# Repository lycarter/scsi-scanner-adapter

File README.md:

# scsi-scanner-adapter

Bringing a Howtek Scanmaster D4000 drum scanner (1990s, SCSI-2) to modern computers
with custom hardware (USB-C ↔ SCSI) and open scanning software.

## Status

Phase 0: requirements and architecture decisions.

## Phases

| # | Folder | What |
|---|--------|------|
| 1 | [`design_docs/1-bus-capture/`](design_docs/1-bus-capture/NOTES.md) | Logic analyzer, passive tap and capture tooling for watching the G4 ↔ scanner bus |
| 2 | [`design_docs/2-reverse-engineering/`](design_docs/2-reverse-engineering/NOTES.md) | Decode the command set and data flow (bus captures + firmware/software analysis) |
| 3 | [`design_docs/3-driver/`](design_docs/3-driver/NOTES.md) | USB-C ↔ SCSI initiator PCB that also works as a listen-only bus sniffer |
| 4 | [`design_docs/4-software/`](design_docs/4-software/NOTES.md) | Driver firmware and host scanning software |

Shared background: [`docs/scanner-facts.md`](docs/scanner-facts.md), [`docs/reference-inventory.md`](docs/reference-inventory.md), [`docs/decisions.md`](docs/decisions.md).

## Known-good baseline

A Power Mac G4 on Mac OS 9, running SilverFast, scans successfully with this scanner.

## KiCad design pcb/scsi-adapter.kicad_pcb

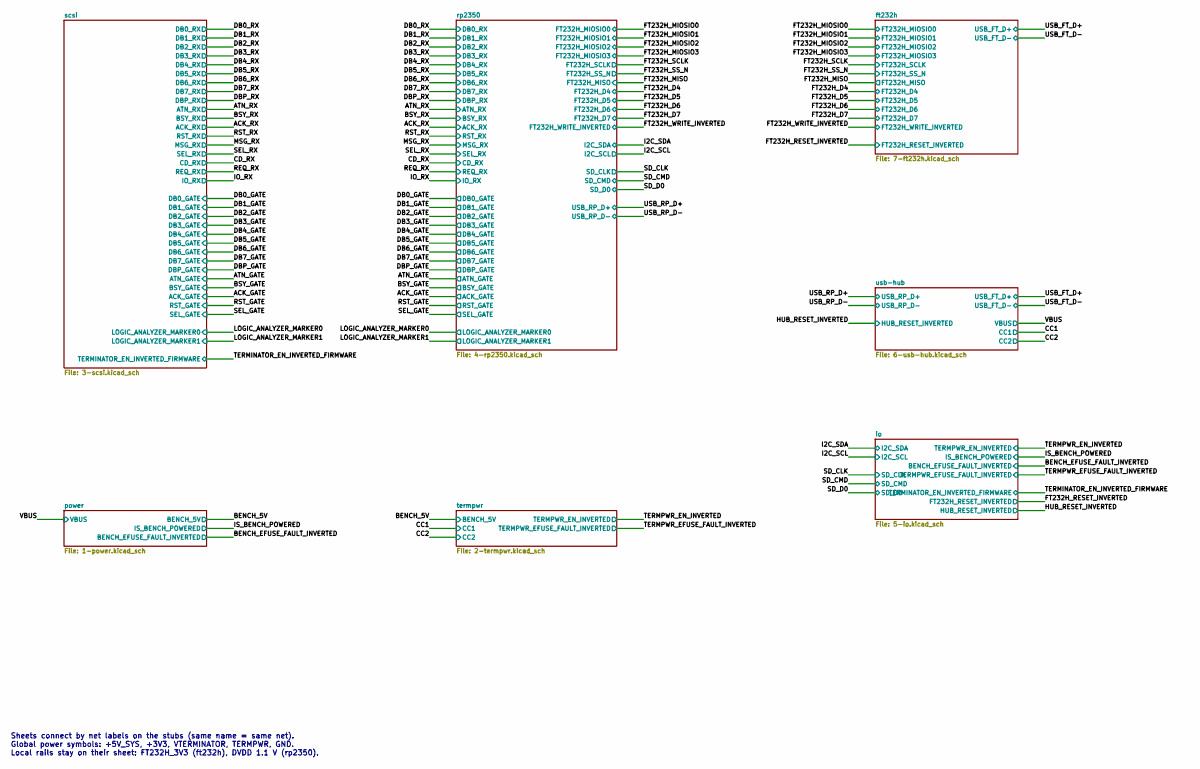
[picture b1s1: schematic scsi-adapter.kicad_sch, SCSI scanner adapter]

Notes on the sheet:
Sheets connect by net labels on the stubs (same name = same net). Global power symbols: +5V_SYS, +3V3, VTERMINATOR, TERMPWR, GND. Local rails stay on their sheet: FT232H_3V3 (ft232h), DVDD 1.1 V (rp2350).

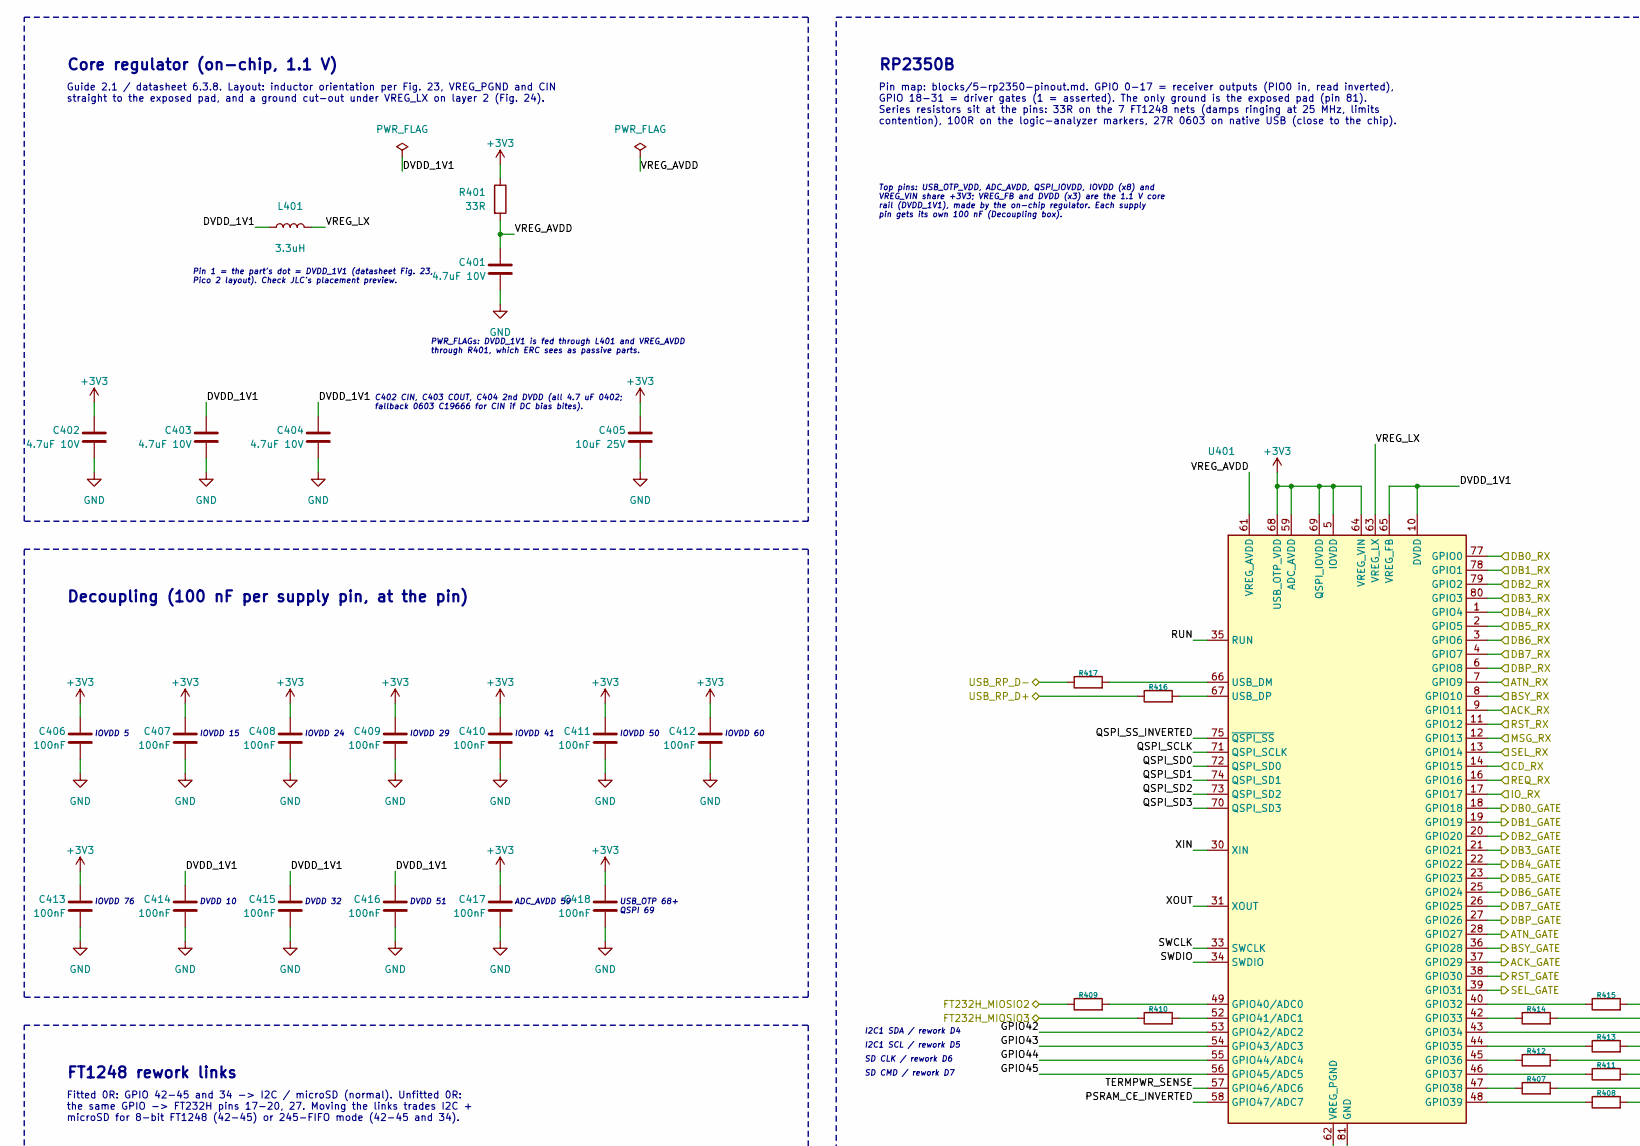
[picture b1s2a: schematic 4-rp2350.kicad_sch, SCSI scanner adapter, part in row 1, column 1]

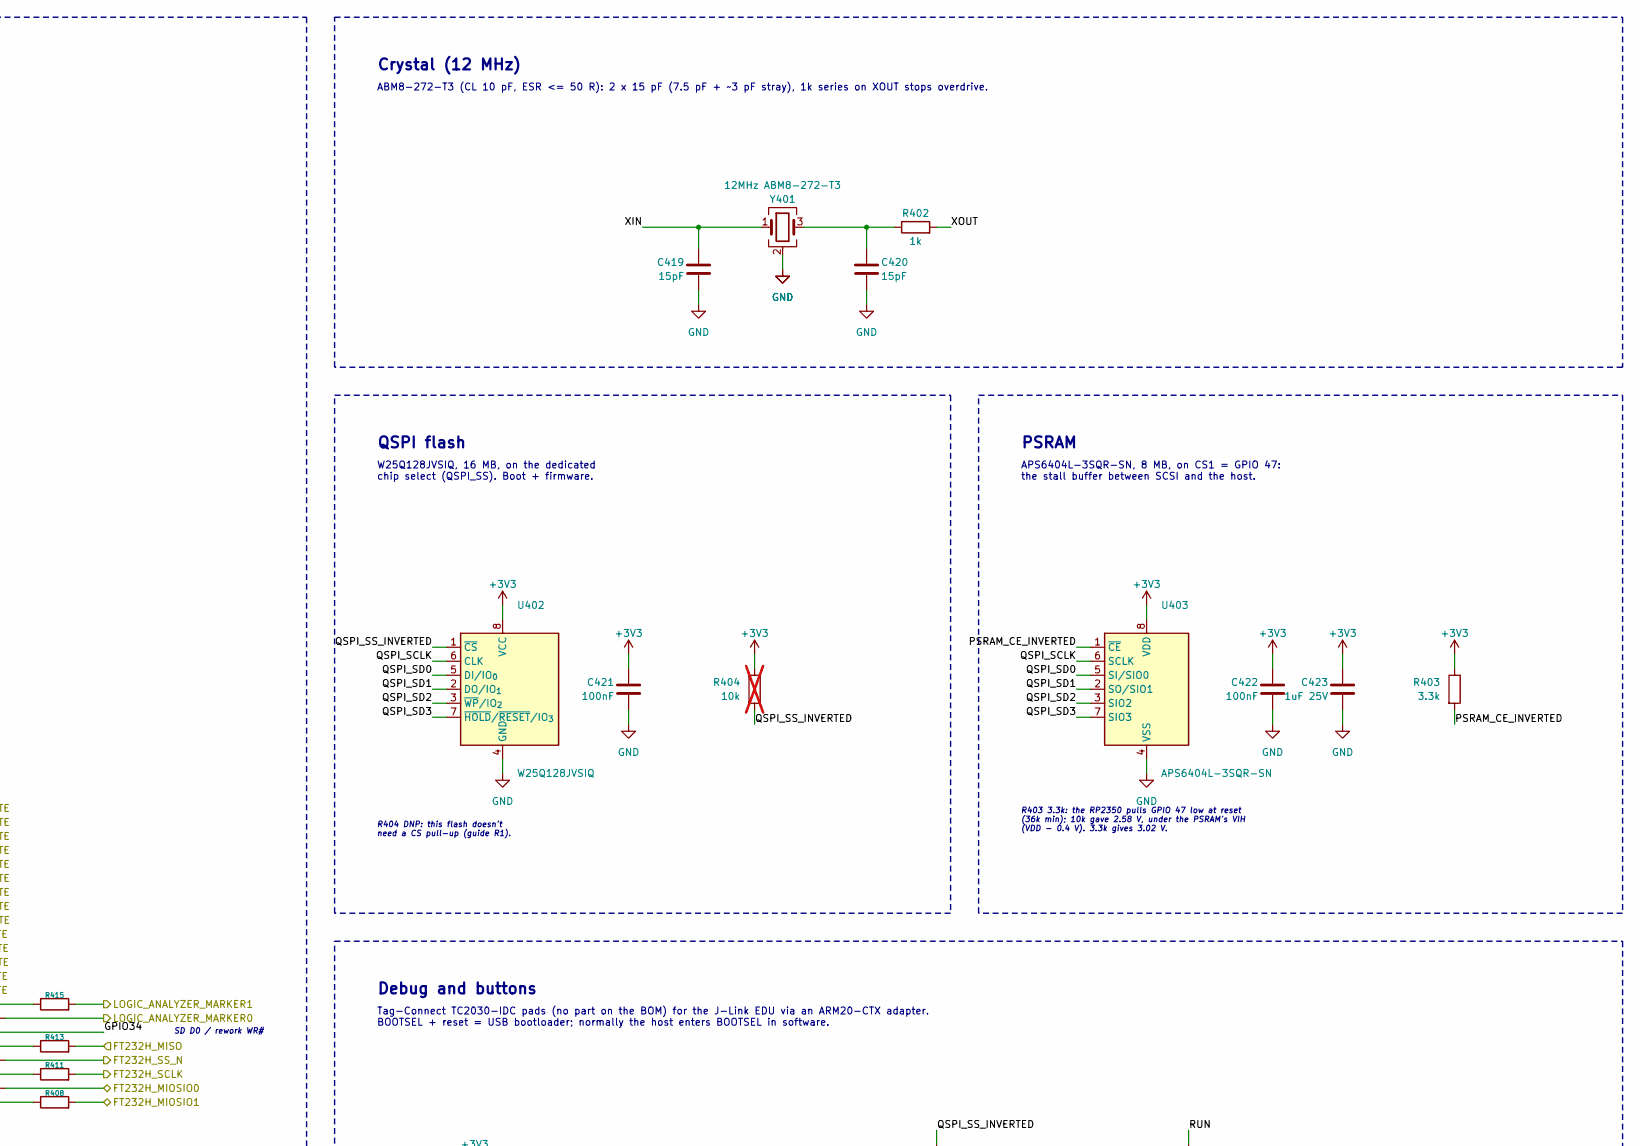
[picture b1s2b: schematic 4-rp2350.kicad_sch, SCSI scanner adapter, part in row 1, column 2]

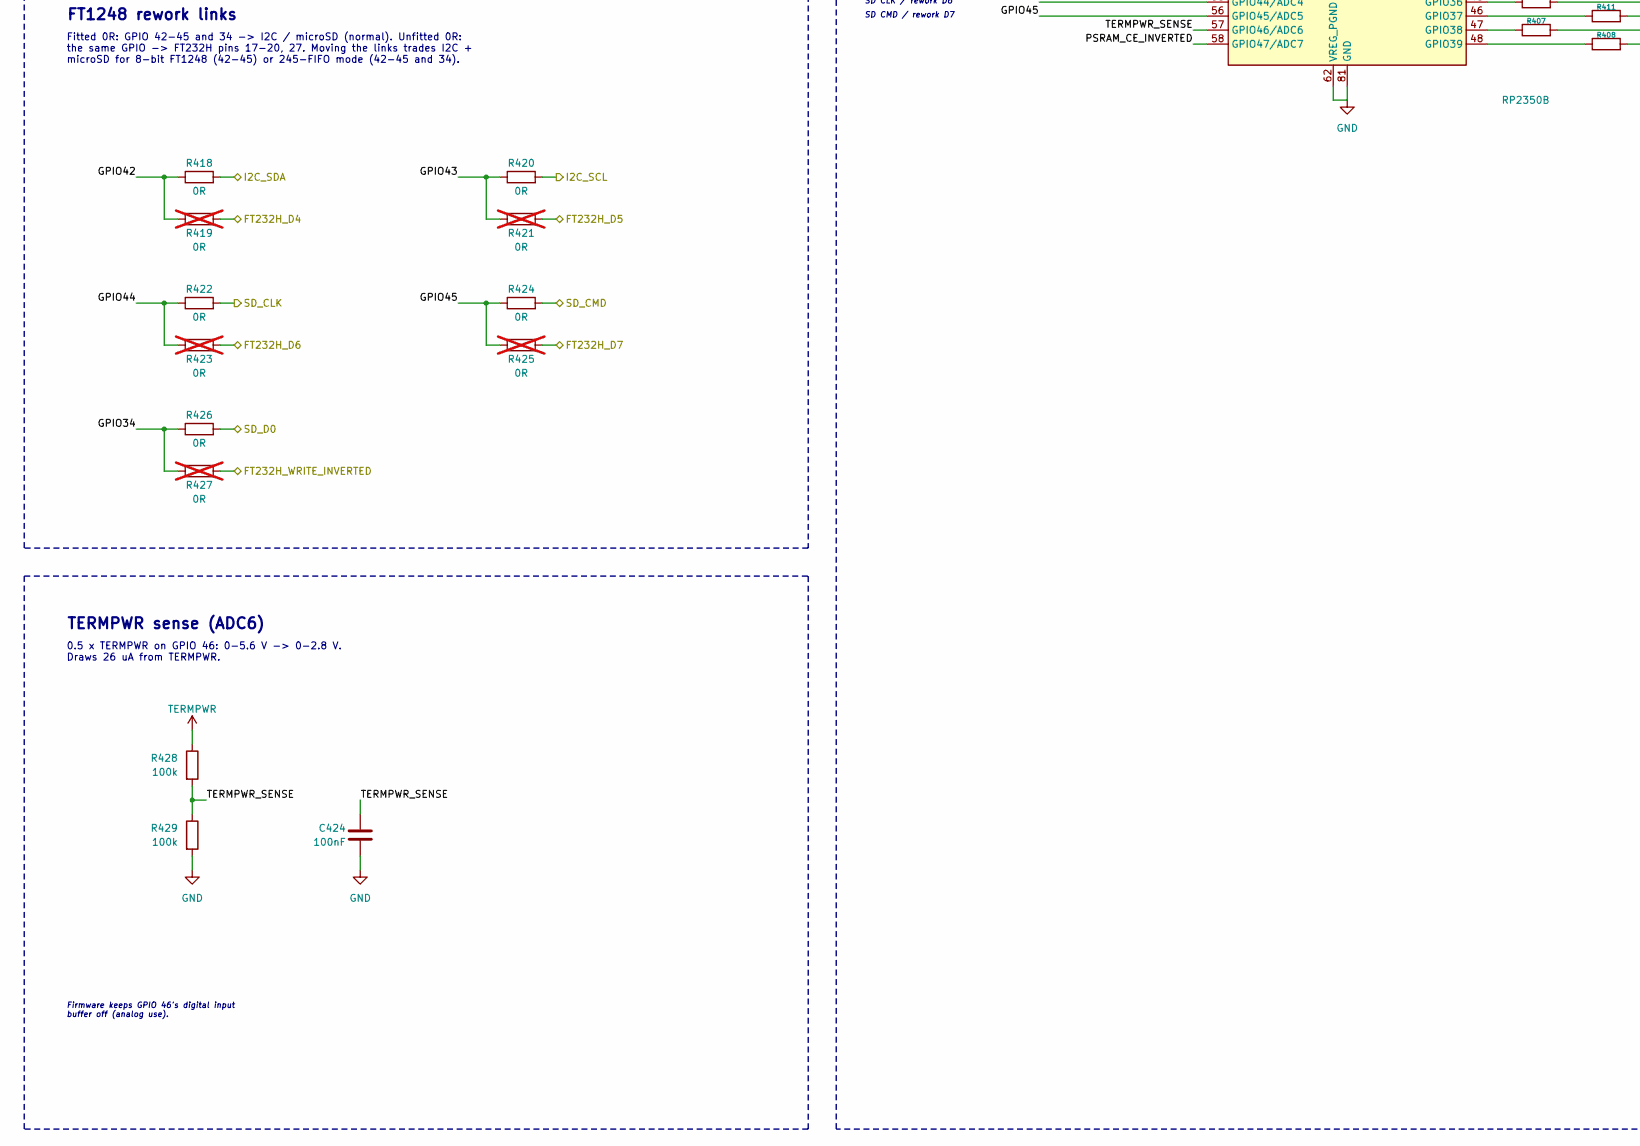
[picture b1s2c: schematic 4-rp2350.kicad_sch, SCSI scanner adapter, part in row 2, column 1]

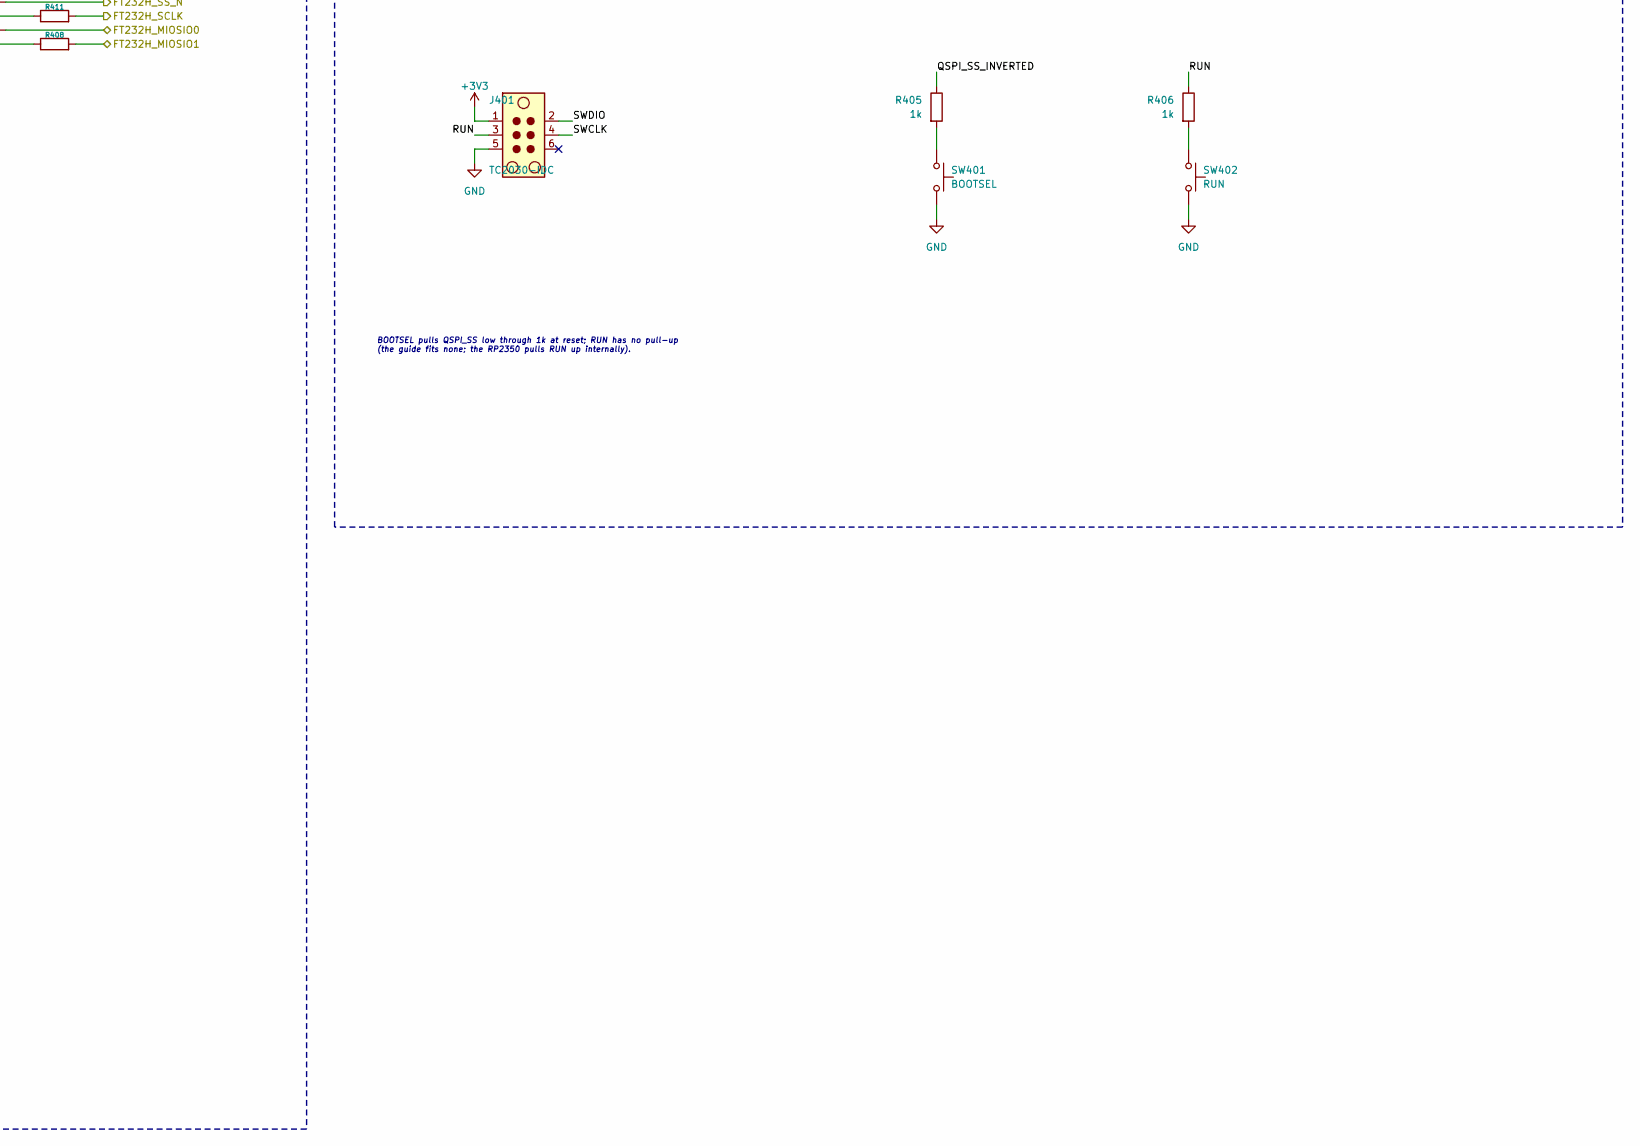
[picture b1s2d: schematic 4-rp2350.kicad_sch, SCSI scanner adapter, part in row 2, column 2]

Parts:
C401, C404: 4.7uF 10V; C_0402_1005Metric; LCSC C23733
C402, C403: 4.7uF 10V; C_0402_1005Metric_Wide; LCSC C23733
C405: 10uF 25V; C_0805_2012Metric; LCSC C15850
C406, C407, C408, C409, C410, C411, C412, C413, C414, C415, C416, C417, C418, C421, C422, C424: 100nF; C_0402_1005Metric; LCSC C307331
C419, C420: 15pF; C_0402_1005Metric; LCSC C1548
C423: 1uF 25V; C_0402_1005Metric; LCSC C52923
J401: TC2030-IDC; Tag-Connect_TC2030-IDC-FP_2x03_P1.27mm_Vertical
L401: 3.3uH; L_Abracon_AOTA-B201610_2.0x1.6mm_Polarized; LCSC C42411119
R401, R407, R408, R409, R410, R411, R412, R413: 33R; R_0402_1005Metric; LCSC C25105
R402, R405, R406: 1k; R_0402_1005Metric; LCSC C11702
R403: 3.3k; R_0402_1005Metric; LCSC C25890
R404: 10k; R_0402_1005Metric; LCSC C25744; not fitted
R414, R415: 100R; R_0402_1005Metric; LCSC C25076
R416, R417: 27R; R_0603_1608Metric; LCSC C25190
R418, R420, R422, R424, R426: 0R; R_0402_1005Metric; LCSC C17168
R419, R421, R423, R425, R427: 0R; R_0805_2012Metric; LCSC C17477; not fitted
R428, R429: 100k; R_0402_1005Metric; LCSC C25741
SW401: BOOTSEL; SW_PUSH_6mm; LCSC C110153
SW402: RUN; SW_PUSH_6mm; LCSC C110153
U401: RP2350B; QFN-80-1EP_10x10mm_P0.4mm_EP3.4x3.4mm; LCSC C42415655
U402: W25Q128JVSIQ; SOIC-8_5.3x5.3mm_P1.27mm; LCSC C97521
U403: APS6404L-3SQR-SN; SOIC-8_3.9x4.9mm_P1.27mm; LCSC C5333729
Y401: 12MHz ABM8-272-T3; Crystal_SMD_3225-4Pin_3.2x2.5mm; LCSC C20625731

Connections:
+3V3: C402.1, C405.1, C406.1, C407.1, C408.1, C409.1, C410.1, C411.1, C412.1, C413.1, C417.1, C418.1, C421.1, C422.1, C423.1, J401.1, R401.1, R403.1, R404.1, U401.5 (IOVDD), U401.15 (IOVDD), U401.24 (IOVDD), U401.29 (IOVDD), U401.41 (IOVDD), U401.50 (IOVDD), U401.59 (ADC_AVDD), U401.60 (IOVDD), U401.64 (VREG_VIN), U401.68 (USB_OTP_VDD), U401.69 (QSPI_IOVDD), U401.76 (IOVDD), U402.8 (VCC), U403.8 (VDD); also elsewhere on the board
/ACK_GATE: U401.37 (GPIO29); also elsewhere on the board
/ACK_RX: U401.9 (GPIO11); also elsewhere on the board
/ATN_GATE: U401.28 (GPIO27); also elsewhere on the board
/ATN_RX: U401.7 (GPIO9); also elsewhere on the board
/BSY_GATE: U401.36 (GPIO28); also elsewhere on the board
/BSY_RX: U401.8 (GPIO10); also elsewhere on the board
/CD_RX: U401.14 (GPIO15); also elsewhere on the board
/DB0_GATE: U401.18 (GPIO18); also elsewhere on the board
/DB0_RX: U401.77 (GPIO0); also elsewhere on the board
/DB1_GATE: U401.19 (GPIO19); also elsewhere on the board
/DB1_RX: U401.78 (GPIO1); also elsewhere on the board
/DB2_GATE: U401.20 (GPIO20); also elsewhere on the board
/DB2_RX: U401.79 (GPIO2); also elsewhere on the board
/DB3_GATE: U401.21 (GPIO21); also elsewhere on the board
/DB3_RX: U401.80 (GPIO3); also elsewhere on the board
/DB4_GATE: U401.22 (GPIO22); also elsewhere on the board
/DB4_RX: U401.1 (GPIO4); also elsewhere on the board
/DB5_GATE: U401.23 (GPIO23); also elsewhere on the board
/DB5_RX: U401.2 (GPIO5); also elsewhere on the board
/DB6_GATE: U401.25 (GPIO24); also elsewhere on the board
/DB6_RX: U401.3 (GPIO6); also elsewhere on the board
/DB7_GATE: U401.26 (GPIO25); also elsewhere on the board
/DB7_RX: U401.4 (GPIO7); also elsewhere on the board
/DBP_GATE: U401.27 (GPIO26); also elsewhere on the board
/DBP_RX: U401.6 (GPIO8); also elsewhere on the board
/FT232H_D4: R419.2; also elsewhere on the board
/FT232H_D5: R421.2; also elsewhere on the board
/FT232H_D6: R423.2; also elsewhere on the board
/FT232H_D7: R425.2; also elsewhere on the board
/FT232H_MIOSIO0: R407.2; also elsewhere on the board
/FT232H_MIOSIO1: R408.2; also elsewhere on the board
/FT232H_MIOSIO2: R409.1; also elsewhere on the board
/FT232H_MIOSIO3: R410.1; also elsewhere on the board
/FT232H_MISO: R413.2; also elsewhere on the board
/FT232H_SCLK: R411.2; also elsewhere on the board
/FT232H_SS_N: R412.2; also elsewhere on the board
/FT232H_WRITE_INVERTED: R427.2; also elsewhere on the board
/I2C_SCL: R420.2; also elsewhere on the board
/I2C_SDA: R418.2; also elsewhere on the board
/IO_RX: U401.17 (GPIO17); also elsewhere on the board
/LOGIC_ANALYZER_MARKER0: R414.2; also elsewhere on the board
/LOGIC_ANALYZER_MARKER1: R415.2; also elsewhere on the board
/MSG_RX: U401.12 (GPIO13); also elsewhere on the board
/REQ_RX: U401.16 (GPIO16); also elsewhere on the board
/RST_GATE: U401.38 (GPIO30); also elsewhere on the board
/RST_RX: U401.11 (GPIO12); also elsewhere on the board
/SD_CLK: R422.2; also elsewhere on the board
/SD_CMD: R424.2; also elsewhere on the board
/SD_D0: R426.2; also elsewhere on the board
/SEL_GATE: U401.39 (GPIO31); also elsewhere on the board
/SEL_RX: U401.13 (GPIO14); also elsewhere on the board
/USB_RP_D+: R416.1; also elsewhere on the board
/USB_RP_D-: R417.1; also elsewhere on the board
/rp2350/DVDD_1V1: C403.1, C404.1, C414.1, C415.1, C416.1, L401.1, U401.10 (DVDD), U401.32 (DVDD), U401.51 (DVDD), U401.65 (VREG_FB)
/rp2350/GPIO34: R426.1, R427.1, U401.43 (GPIO34)
/rp2350/GPIO42: R418.1, R419.1, U401.53 (GPIO42/ADC2)
/rp2350/GPIO43: R420.1, R421.1, U401.54 (GPIO43/ADC3)
/rp2350/GPIO44: R422.1, R423.1, U401.55 (GPIO44/ADC4)
/rp2350/GPIO45: R424.1, R425.1, U401.56 (GPIO45/ADC5)
/rp2350/PSRAM_CE_INVERTED: R403.2, U401.58 (GPIO47/ADC7), U403.1 (~CE)
/rp2350/QSPI_SCLK: U401.71 (QSPI_SCLK), U402.6 (CLK), U403.6 (SCLK)
/rp2350/QSPI_SD0: U401.72 (QSPI_SD0), U402.5 (DI/IO_{0}), U403.5 (SI/SIO0)
/rp2350/QSPI_SD1: U401.74 (QSPI_SD1), U402.2 (DO/IO_{1}), U403.2 (SO/SIO1)
/rp2350/QSPI_SD2: U401.73 (QSPI_SD2), U402.3 (~WP/IO_{2}), U403.3 (SIO2)
/rp2350/QSPI_SD3: U401.70 (QSPI_SD3), U402.7 (~HOLD/~RESET/IO_{3}), U403.7 (SIO3)
/rp2350/QSPI_SS_INVERTED: R404.2, R405.1, U401.75 (~QSPI_SS), U402.1 (~CS)
/rp2350/RUN: J401.3, R406.1, U401.35 (RUN)
/rp2350/SWCLK: J401.4, U401.33 (SWCLK)
/rp2350/SWDIO: J401.2, U401.34 (SWDIO)
/rp2350/TERMPWR_SENSE: C424.1, R428.2, R429.1, U401.57 (GPIO46/ADC6)
/rp2350/VREG_AVDD: C401.1, R401.2, U401.61 (VREG_AVDD)
/rp2350/VREG_LX: L401.2, U401.63 (VREG_LX)
/rp2350/XIN: C419.1, U401.30 (XIN), Y401.1
/rp2350/XOUT: R402.2, U401.31 (XOUT)
GND: C401.2, C402.2, C403.2, C404.2, C405.2, C406.2, C407.2, C408.2, C409.2, C410.2, C411.2, C412.2, C413.2, C414.2, C415.2, C416.2, C417.2, C418.2, C419.2, C420.2, C421.2, C422.2, C423.2, C424.2, J401.5, R429.2, SW401.2, SW402.2, U401.62 (VREG_PGND), U401.81 (GND), U402.4 (GND), U403.4 (VSS), Y401.2 (G), Y401.4 (G); also elsewhere on the board
unnamed: C420.1, R402.1, Y401.3
unnamed: R405.2, SW401.1
unnamed: R406.2, SW402.1
unnamed: R415.1, U401.40 (GPIO32)
unnamed: R414.1, U401.42 (GPIO33)
unnamed: R413.1, U401.44 (GPIO35)
unnamed: R412.1, U401.45 (GPIO36)
unnamed: R411.1, U401.46 (GPIO37)
unnamed: R407.1, U401.47 (GPIO38)
unnamed: R408.1, U401.48 (GPIO39)
unnamed: R409.2, U401.49 (GPIO40/ADC0)
unnamed: R410.2, U401.52 (GPIO41/ADC1)
unnamed: R417.2, U401.66 (USB_DM)
unnamed: R416.2, U401.67 (USB_DP)
TERMPWR: R428.1; also elsewhere on the board

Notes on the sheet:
BOOTSEL pulls QSPI_SS low through 1k at reset; RUN has no pull-up (the guide fits none; the RP2350 pulls RUN up internally).
USB_OTP 68+ QSPI 69
R404 DNP: this flash doesn't need a CS pull-up (guide R1).
PWR_FLAGs: DVDD_1V1 is fed through L401 and VREG_AVDD through R401, which ERC sees as passive parts.
ADC_AVDD 59
SD CLK / rework D6
I2C1 SDA / rework D4
Tag-Connect TC2030-IDC pads (no part on the BOM) for the J-Link EDU via an ARM20-CTX adapter. BOOTSEL + reset = USB bootloader; normally the host enters BOOTSEL in software.
Pin map: blocks/5-rp2350-pinout.md. GPIO 0-17 = receiver outputs (PIO0 in, read inverted), GPIO 18-31 = driver gates (1 = asserted). The only ground is the exposed pad (pin 81). Series resistors sit at the pins: 33R on the 7 FT1248 nets (damps ringing at 25 MHz, limits contention), 100R on the logi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
IOVDD 41
IOVDD 24
Firmware keeps GPIO 46's digital input buffer off (analog use).
IOVDD 50
W25Q128JVSIQ, 16 MB, on the dedicated chip select (QSPI_SS). Boot + firmware.
IOVDD 29
DVDD 10
Fitted 0R: GPIO 42-45 and 34 -> I2C / microSD (normal). Unfitted 0R: the same GPIO -> FT232H pins 17-20, 27. Moving the links trades I2C + microSD for 8-bit FT1248 (42-45) or 245-FIFO mode (42-45 and 34).
DVDD 51
ABM8-272-T3 (CL 10 pF, ESR <= 50 R): 2 x 15 pF (7.5 pF + ~3 pF stray), 1k series on XOUT stops overdrive.
Pin 1 = the part's dot = DVDD_1V1 (datasheet Fig. 23, Pico 2 layout). Check JLC's placement preview.
IOVDD 15
Guide 2.1 / datasheet 6.3.8. Layout: inductor orientation per Fig. 23, VREG_PGND and CIN straight to the exposed pad, and a ground cut-out under VREG_LX on layer 2 (Fig. 24).
PSRAM
APS6404L-3SQR-SN, 8 MB, on CS1 = GPIO 47: the stall buffer between SCSI and the host.
QSPI flash
IOVDD 76
SD CMD / rework D7
Core regulator (on-chip, 1.1 V)
FT1248 rework links
R403 3.3k: the RP2350 pulls GPIO 47 low at reset (36k min); 10k gave 2.58 V, under the PSRAM's VIH (VDD - 0.4 V). 3.3k gives 3.02 V.
DVDD 32
C402 CIN, C403 COUT, C404 2nd DVDD (all 4.7 uF 0402; fallback 0603 C19666 for CIN if DC bias bites).
RP2350B
0.5 x TERMPWR on GPIO 46: 0-5.6 V -> 0-2.8 V. Draws 26 uA from TERMPWR.
Decoupling (100 nF per supply pin, at the pin)
Debug and buttons
SD D0 / rework WR#
Crystal (12 MHz)
IOVDD 5
Top pins: USB_OTP_VDD, ADC_AVDD, QSPI_IOVDD, IOVDD (x8) and VREG_VIN share +3V3; VREG_FB and DVDD (x3) are the 1.1 V core rail (DVDD_1V1), made by the on-chip regulator. Each supply pin gets its own 100 nF (Decoupling box).

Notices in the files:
pcb/scsi-adapter.kicad_pcb:
MIT License
